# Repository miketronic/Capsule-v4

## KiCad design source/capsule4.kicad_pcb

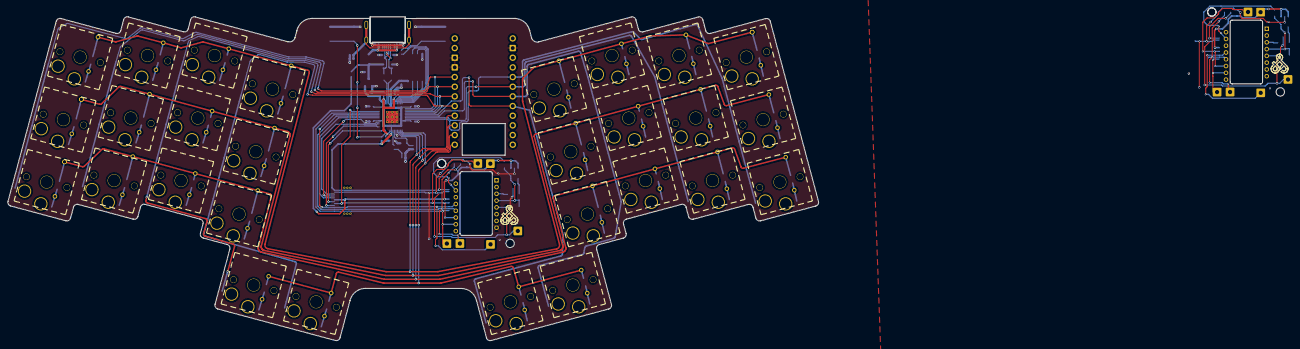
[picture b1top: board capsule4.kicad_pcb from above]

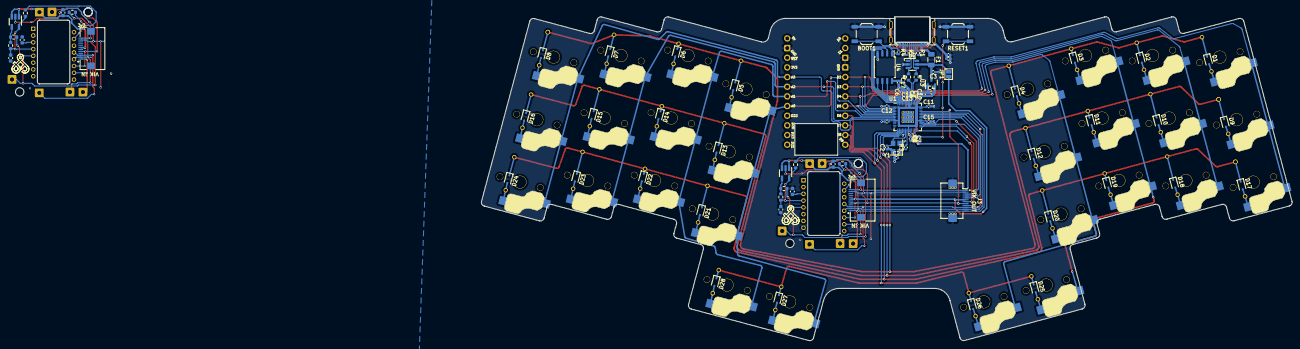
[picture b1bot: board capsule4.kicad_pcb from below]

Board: 2 copper layers, 213.0 x 85.1 mm, 127 parts (85 on the bottom side), 75 nets.

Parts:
BOOT1: B; SW_SPST_TL3342
C2, C2#2: 22pF; C_0402_1005Metric
C3, C4, C5: 1uF; C_0402_1005Metric
C6, C7, C8, C9, C10, C11, C12, C13, C14, C15, C16, C17: 100nF; C_0402_1005Metric
C1001, C1001#2: 4.7uF; C_0603_1608Metric
C1002, C1002#2, C1005, C1005#2: 1uF; C_0603_1608Metric
C_Shield1: 4.7n; C_0402_1005Metric
D1, D2, D3, D4, D5, D6, D7, D8, D9, D10, D11, D12, D13, D14, D15, D16, D17, D18, D19, D20, D21, D22, D23, D24, D25, D26, D27, D28: D; D_SOD-323
F1: 500mA; Fuse_1206_3216Metric
IC1001, IC1001#2: AP7335-WG-7; SOT-23-5_HandSoldering
J1: USB_C; MB_Molex-216990_USB_TYPE-C
J2, J4: Conn_01x12; PinHeader_1x12_P2.54mm
J3: VIK Keyboard Expansion; VIK_Keyboard_Horizontal
J1001, J1001#2, J1002, J1002#2, J1004, J1004#2, J1005, J1005#2, J1006, J1006#2, J1007, J1007#2: Conn_01x01_Socket; SolderWire-0.5sqmm_1x01_D0.9mm_OD2.3mm
J1003, J1003#2: vik-module-connector-horizontal
JP1: 5V_EN; SolderJumper-2_P1.3mm_Open_Pad1.0x1.5mm
R1, R2: 5.1k; R_0402_1005Metric
R3, R4: 1k; R_0402_1005Metric
R5: 10k; R_0402_1005Metric
R6, R7: 27R; R_0603_1608Metric
R1001, R1001#2, R1004, R1004#2: 10k; R_0603_1608Metric
R1002, R1002#2: 39; R_0603_1608Metric
R1003, R1003#2: 15k; R_0603_1608Metric
RESET1: R; SW_SPST_TL3342
R_Shield1: 1M; R_0402_1005Metric
SW1, SW2, SW3, SW4, SW5, SW6, SW7, SW8, SW9, SW10, SW11, SW12, SW13, SW14, SW15, SW16, SW17, SW18, SW19, SW20, SW21, SW22, SW23, SW24, SW25, SW26, SW27, SW28: SW; MB_KailhChoc-1U_HS_17mm
U1: RP2040; MB_RP2040-QFN-56
U2: SRV05-4; SOT-23-6-routable
U3: XC6206; SOT-23
U4: W25Q128JVS; SOIC-8_5.23x5.23mm_P1.27mm
U1001, U1001#2: PMW3360DM-T2QU; DIP-16_W10.16mm
Y1: 12MHz; Crystal_SMD_3225-4Pin_3.2x2.5mm

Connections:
+1V1: C5.1, C6.1, C7.1, U1.23 (DVDD), U1.45 (VREG_VOUT), U1.50 (DVDD)
+3V3: C4.2, C8.1, C9.1, C10.1, C11.1, C12.1, C13.1, C14.1, C15.1, C16.1, C17.1, J3.1 (3V3), J4.9, J1001.1, J1001#2.1, J1003.12 (3V3), J1003#2.12 (3V3), R5.1, R1001.1, R1001#2.1, U1.1 (IOVDD), U1.10 (IOVDD), U1.22 (IOVDD), U1.33 (IOVDD), U1.42 (IOVDD), U1.43 (ADC_AVDD), U1.44 (VREG_VIN), U1.48 (USB_VDD), U1.49 (IOVDD), U3.2 (VO), U4.8 (VCC), U1001.5 (VDDIO), U1001#2.5 (VDDIO)
+5V: C3.2, F1.2, J4.12, JP1.2 (B), U2.5 (VP), U3.3 (VI)
/CC1: J1.A5 (CC1), R1.1
/CC2: J1.B5 (CC2), R2.1
/D_+: R6.2, U1.47 (D+)
/D_-: R7.2, U1.46 (D-)
/XTAL_O: C2.2, R3.1, Y1.1
/~USB_BOOT: BOOT1.1, R4.1
COL0: J2.5, SW1.1, SW9.1, SW17.1, U1.2 (GPIO0)
COL1: J2.6, SW2.1, SW10.1, SW18.1, U1.3 (GPIO1)
COL2: J2.7, SW3.1, SW11.1, SW19.1, SW25.1, U1.4 (GPIO2)
COL3: J2.8, SW4.1, SW12.1, SW20.1, SW26.1, U1.5 (GPIO3)
COL4: J4.5, SW5.1, SW13.1, SW21.1, SW27.1, U1.6 (GPIO4)
COL5: J4.6, SW6.1, SW14.1, SW22.1, SW28.1, U1.7 (GPIO5)
COL6: J4.7, SW7.1, SW15.1, SW23.1, U1.8 (GPIO6)
COL7: J4.8, SW8.1, SW16.1, SW24.1, U1.9 (GPIO7)
CS: R4.2, U1.56 (QSPI_SS_N), U4.1 (~CS)
DBUS+: J1.A6 (D+), J1.B6 (D+), R6.1, U2.3 (IO2)
DBUS-: J1.A7 (D-), J1.B7 (D-), R7.1, U2.4 (IO3)
GND: BOOT1.2, C2.1, C2#2.1, C3.1, C4.1, C5.2, C6.2, C7.2, C8.2, C9.2, C10.2, C11.2, C12.2, C13.2, C14.2, C15.2, C16.2, C17.2, C1001.2, C1001#2.2, C1002.2, C1002#2.2, C1005.2, C1005#2.2, C_Shield1.1, IC1001.2 (GND), IC1001#2.2 (GND), J1.A1 (GND), J1.A12 (GND), J1.B1 (GND), J1.B12 (GND), J2.3, J2.4, J3.2 (GND), J3.MP, J4.11, J1003.11 (GND), J1003#2.11 (GND), R1.2, R2.2, R1004.2, R1004#2.2, RESET1.2, R_Shield1.2, U1.19 (TESTEN), U1.57 (GND), U2.2 (VN), U3.1 (GND), U4.4 (GND), U1001.8 (GND), U1001#2.8 (GND), Y1.2, Y1.4
GNDREF: C_Shield1.2, J1.S1 (SHIELD), R_Shield1.1
MISO: J3.11 (MISO), J1003.2 (MISO), J1003#2.2 (MISO), J1004.1, J1004#2.1, R1001.2, R1001#2.2, U1.36 (GPIO24), U1001.12 (MISO), U1001#2.12 (MISO)
MOSI: J3.8 (MOSI), J1003.5 (MOSI), J1003#2.5 (MOSI), J1006.1, J1006#2.1, U1.39 (GPIO27/ADC1), U1001.11 (MOSI), U1001#2.11 (MOSI)
NCS: J3.10 (CS), J1003.3 (SPI_CS), J1003#2.3 (SPI_CS), J1005.1, J1005#2.1, U1.37 (GPIO25), U1001.13 (NCS), U1001#2.13 (NCS)
unnamed: D1.2, SW1.2
unnamed: D2.2, SW2.2
unnamed: D3.2, SW3.2
unnamed: D4.2, SW4.2
unnamed: D5.2, SW5.2
unnamed: D6.2, D7.2, SW6.2, SW7.2
unnamed: D8.2, SW8.2
unnamed: D9.2, D10.2, SW9.2, SW10.2
unnamed: D11.2, SW11.2
unnamed: D12.2, SW12.2
unnamed: D13.2, SW13.2
unnamed: D14.2, SW14.2
unnamed: D15.2, SW15.2
unnamed: D16.2, SW16.2
unnamed: D17.2, SW17.2
unnamed: D18.2, SW18.2
unnamed: D19.2, SW19.2
unnamed: D20.2, SW20.2
unnamed: D21.2, SW21.2
unnamed: D22.2, SW22.2
unnamed: D23.2, SW23.2
unnamed: D24.2, SW24.2
unnamed: D25.2, SW25.2
unnamed: D26.2, SW26.2
unnamed: D27.2, SW27.2
unnamed: D28.2, SW28.2
unnamed: IC1001.4 (ADJ), IC1001#2.4 (ADJ), R1003.1, R1003#2.1, R1004.1, R1004#2.1
unnamed: R1002.2, R1002#2.2, U1001.15 (LED_P), U1001#2.15 (LED_P)
unnamed: C1001.1, C1001#2.1, U1001.3 (VDDPIX), U1001#2.3 (VDDPIX)
QSPI_CLK: U1.52 (QSPI_SCLK), U4.6 (CLK)
RGB: J3.5 (RGB), U1.35 (GPIO23)
ROW0: D1.1, D2.1, D3.1, D4.1, D5.1, D6.1, D7.1, D8.1, J2.9, U1.18 (GPIO15)
ROW1: D9.1, D10.1, D11.1, D12.1, D13.1, D14.1, D15.1, D16.1, J2.10, U1.17 (GPIO14)
ROW2: D17.1, D18.1, D19.1, D20.1, D21.1, D22.1, D23.1, D24.1, J2.11, U1.16 (GPIO13)
ROW3: D25.1, D26.1, D27.1, D28.1, J2.12, U1.15 (GPIO12)
SCL: J3.4 (SCL), U1.32 (GPIO21)
SCLK: J3.12 (SCLK), J1002.1, J1002#2.1, J1003.1 (SCLK), J1003#2.1 (SCLK), U1.38 (GPIO26/ADC0), U1001.10 (SCLK), U1001#2.10 (SCLK)
SD0: U1.53 (QSPI_SD0), U4.5 (DI(IO0))
SD1: U1.55 (QSPI_SD1), U4.2 (DO(IO1))
SD2: U1.54 (QSPI_SD2), U4.3 (IO2)
SD3: U1.51 (QSPI_SD3), U4.7 (IO3)
SDA: J3.3 (SDA), U1.31 (GPIO20)
VBUS: F1.1, J1.A4 (VBUS), J1.A9 (VBUS), J1.B4 (VBUS), J1.B9 (VBUS)
VDD_2V: C1005.1, C1005#2.1, IC1001.5 (OUT), IC1001#2.5 (OUT), R1002.1, R1002#2.1, R1003.2, R1003#2.2, U1001.4 (VDD), U1001#2.4 (VDD)
VDD_5V: C1002.1, C1002#2.1, IC1001.1 (IN), IC1001.3 (EN), IC1001#2.1 (IN), IC1001#2.3 (EN), J3.6 (5V), J1007.1, J1007#2.1, JP1.1 (A)
VIK_GPIO1: J3.7 (GPIO1), U1.28 (GPIO17)
VIK_GPIO2: J3.9 (GPIO2), U1.29 (GPIO18)
XTAL_IN: C2#2.2, U1.20 (XTAL_IN), Y1.3
XTAL_OUT: R3.2, U1.21 (XTAL_OUT)
~RESET: R5.2, RESET1.1, U1.26 (~RUN)

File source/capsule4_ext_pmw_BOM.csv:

Comment,Designator,Footprint,LCSC
D,"D26,D10,D11,D8,D25,D13,D12,D21,D23,D16,D4,D1,D18,D15,D28,D6,D9,D7,D17,D22,D24,D14,D5,D20,D19,D2,D27,D3",D_SOD-323,C2931613
B,"BOOT,RESET",SW_SPST_TL3342,C115351
27R,"R6,R7",R_0603_1608Metric,C25190
22pF,"C2,C1",C_0402_1005Metric,C1555
5.1k,"R4,R3",R_0402_1005Metric,C25905
1M,R_S,R_0402_1005Metric,C26083
100nF,"C10,C11,C12,C13,C14,C15,C16,C17,C6,C7,C8,C9",C_0402_1005Metric,C1525
RP2040,U1,RP2040-QFN-56,C2040
SRV05-4,U2,SOT-23-6-routable,C85364
10k,R5,R_0402_1005Metric,C25744
1k,"R1,R2",R_0402_1005Metric,C11702
USB_C,J1,Molex-216990_GCT-USB45xx_HRO-TYPE-C-31-M-13x,C223906
1uF,"C5,C3,C4",C_0402_1005Metric,C52923
500mA,F1,Fuse_1206_3216Metric,C70076
4.7n,C_S,C_0402_1005Metric,C1538
"VIK Keyboard Expansion",J3,~,C262661
W25Q128JVS,U4,SOIC-8_5.23x5.23mm_P1.27mm,C97521
12MHz,Y1,Crystal_SMD_3225-4Pin_3.2x2.5mm,C9002
XC6206,U3,SOT-23,C5446

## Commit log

2023-12-08 New repo
